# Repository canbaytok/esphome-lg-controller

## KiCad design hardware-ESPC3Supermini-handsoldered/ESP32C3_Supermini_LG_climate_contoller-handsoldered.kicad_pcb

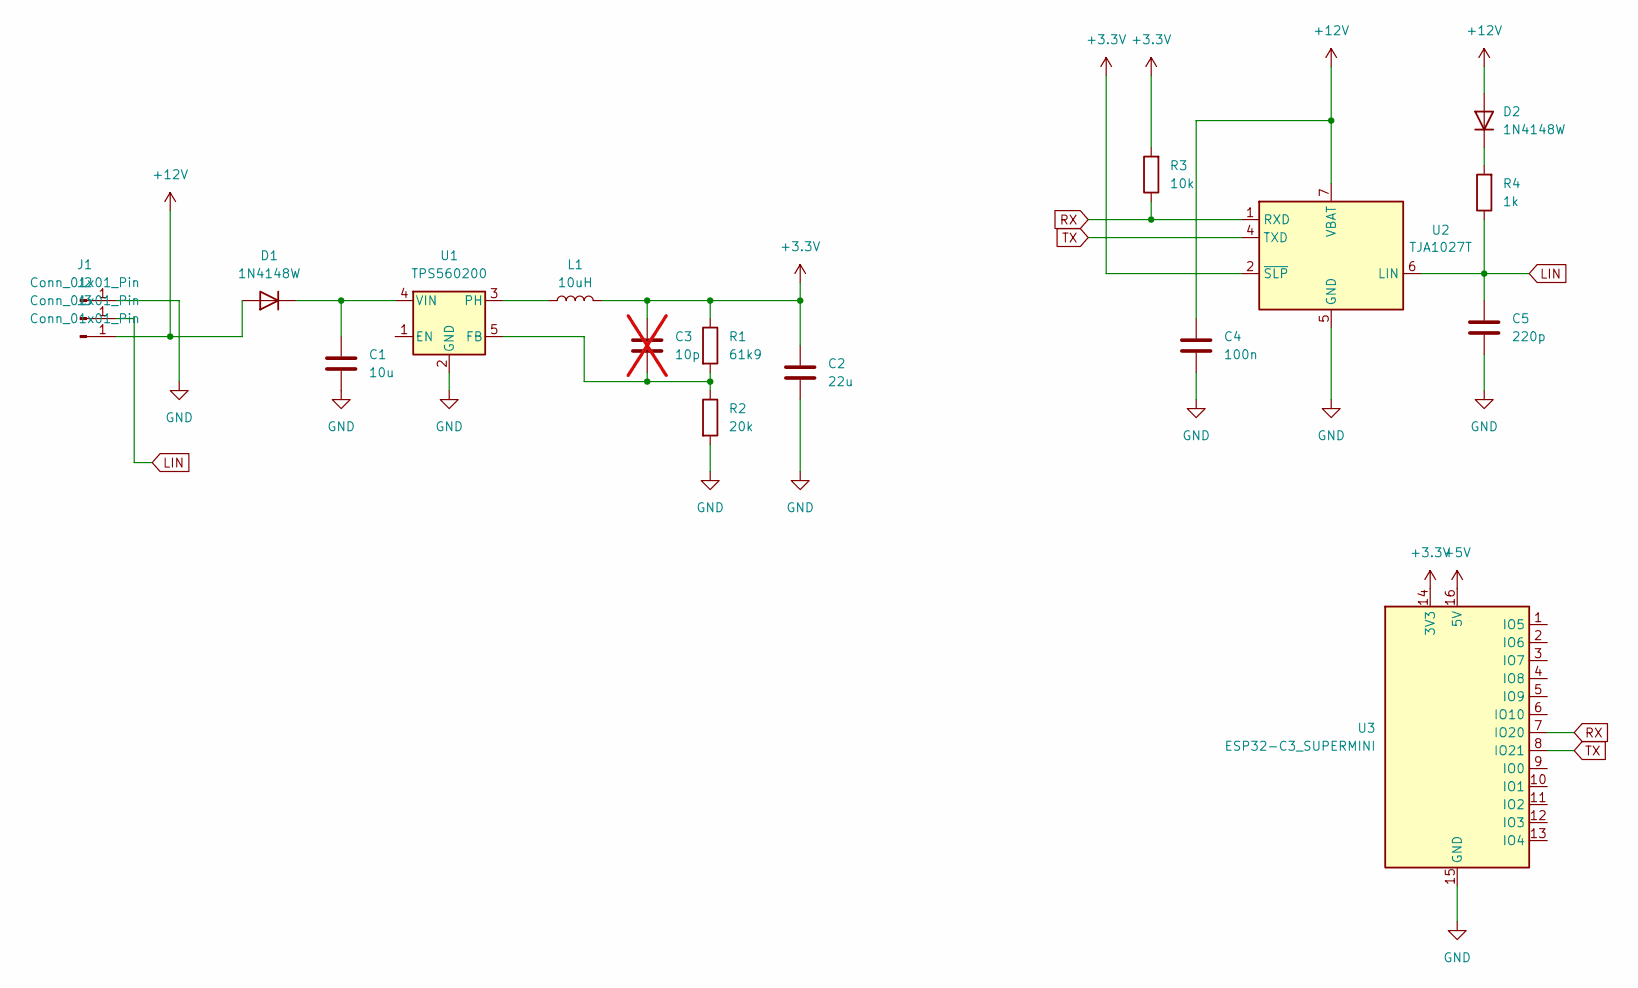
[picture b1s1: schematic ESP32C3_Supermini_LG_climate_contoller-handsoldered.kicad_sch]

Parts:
C1: 10u; C_0805_2012Metric_Pad1.18x1.45mm_HandSolder
C2: 22u; C_0805_2012Metric_Pad1.18x1.45mm_HandSolder
C3: 10p; C_0805_2012Metric_Pad1.18x1.45mm_HandSolder; not fitted
C4: 100n; C_0805_2012Metric_Pad1.18x1.45mm_HandSolder; LCSC C1525
C5: 220p; C_0805_2012Metric_Pad1.18x1.45mm_HandSolder
D1, D2: 1N4148W; D_SOD-123; LCSC C2128
J1, J2, J3: Conn_01x01_Pin; SolderWirePad_1x01_SMD_2x4mm
L1: 10uH; L_Wurth_WE-LQSH-3012; LCSC C5289310
R1: 61k9; R_0805_2012Metric_Pad1.20x1.40mm_HandSolder; LCSC C25912
R2: 20k; R_0805_2012Metric_Pad1.20x1.40mm_HandSolder; LCSC C25765
R3: 10k; R_0805_2012Metric_Pad1.20x1.40mm_HandSolder; LCSC C25744
R4: 1k; R_0805_2012Metric_Pad1.20x1.40mm_HandSolder; LCSC C11702
U1: TPS560200; SOT-23-5; LCSC C83671
U2: TJA1027T; SOIC-8_3.9x4.9mm_P1.27mm; LCSC C194371
U3: ESP32-C3_SUPERMINI; ESP32-C3 SUPERMINI

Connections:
+3.3V: C2.1, C3.1, L1.2, R1.1, R3.2, U2.2 (~SLP), U3.14 (3V3)
+5V: U3.16 (5V)
+12V: C4.1, D1.2 (A), D2.2 (A), J3.1 (Pin_1_1), U2.7 (VBAT)
GND: C1.2, C2.2, C4.2, C5.2, J1.1 (Pin_1_1), R2.2, U1.2 (GND), U2.5 (GND), U3.15 (GND)
LIN: C5.1, J2.1 (Pin_1_1), R4.1, U2.6 (LIN)
unnamed: C1.1, D1.1 (K), U1.4 (VIN)
unnamed: D2.1 (K), R4.2
unnamed: C3.2, R1.2, R2.1, U1.5 (FB)
unnamed: L1.1, U1.3 (PH)
RX: R3.1, U2.1 (RXD), U3.7 (IO20)
TX: U2.4 (TXD), U3.8 (IO21)

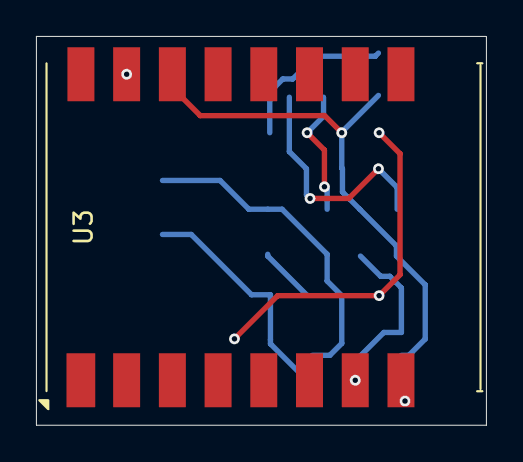
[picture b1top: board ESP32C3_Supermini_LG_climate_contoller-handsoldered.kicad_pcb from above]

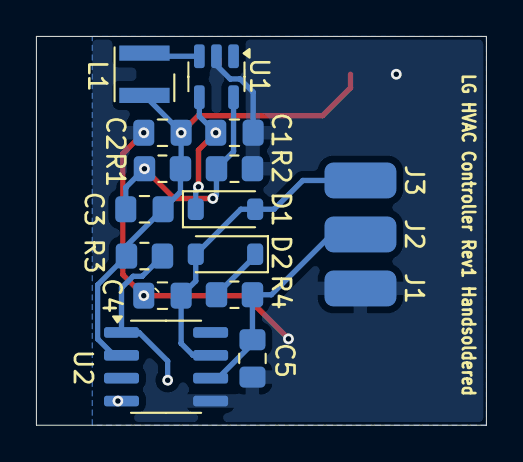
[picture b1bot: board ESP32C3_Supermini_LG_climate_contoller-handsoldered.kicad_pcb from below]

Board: 2 copper layers, 25.0 x 21.6 mm, 18 parts (17 on the bottom side), 10 nets.

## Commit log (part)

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2026-06-23 added handsoldered version for esp32c3-supermini board
2026-06-23 moved silkscreen
